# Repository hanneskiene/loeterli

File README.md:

## Parts needed
* Board
* JBC t245 handpiece
* Transformer 12-24V 50-120VA

## TODO
* Handle holder in pcb?
* Zero Cross Detection
* Termocouple Instrumentation Amp Layout
* Overcurrent Detection with shunt
* Connector for external sleep input + sleep in middle stand
* FUSE to earth

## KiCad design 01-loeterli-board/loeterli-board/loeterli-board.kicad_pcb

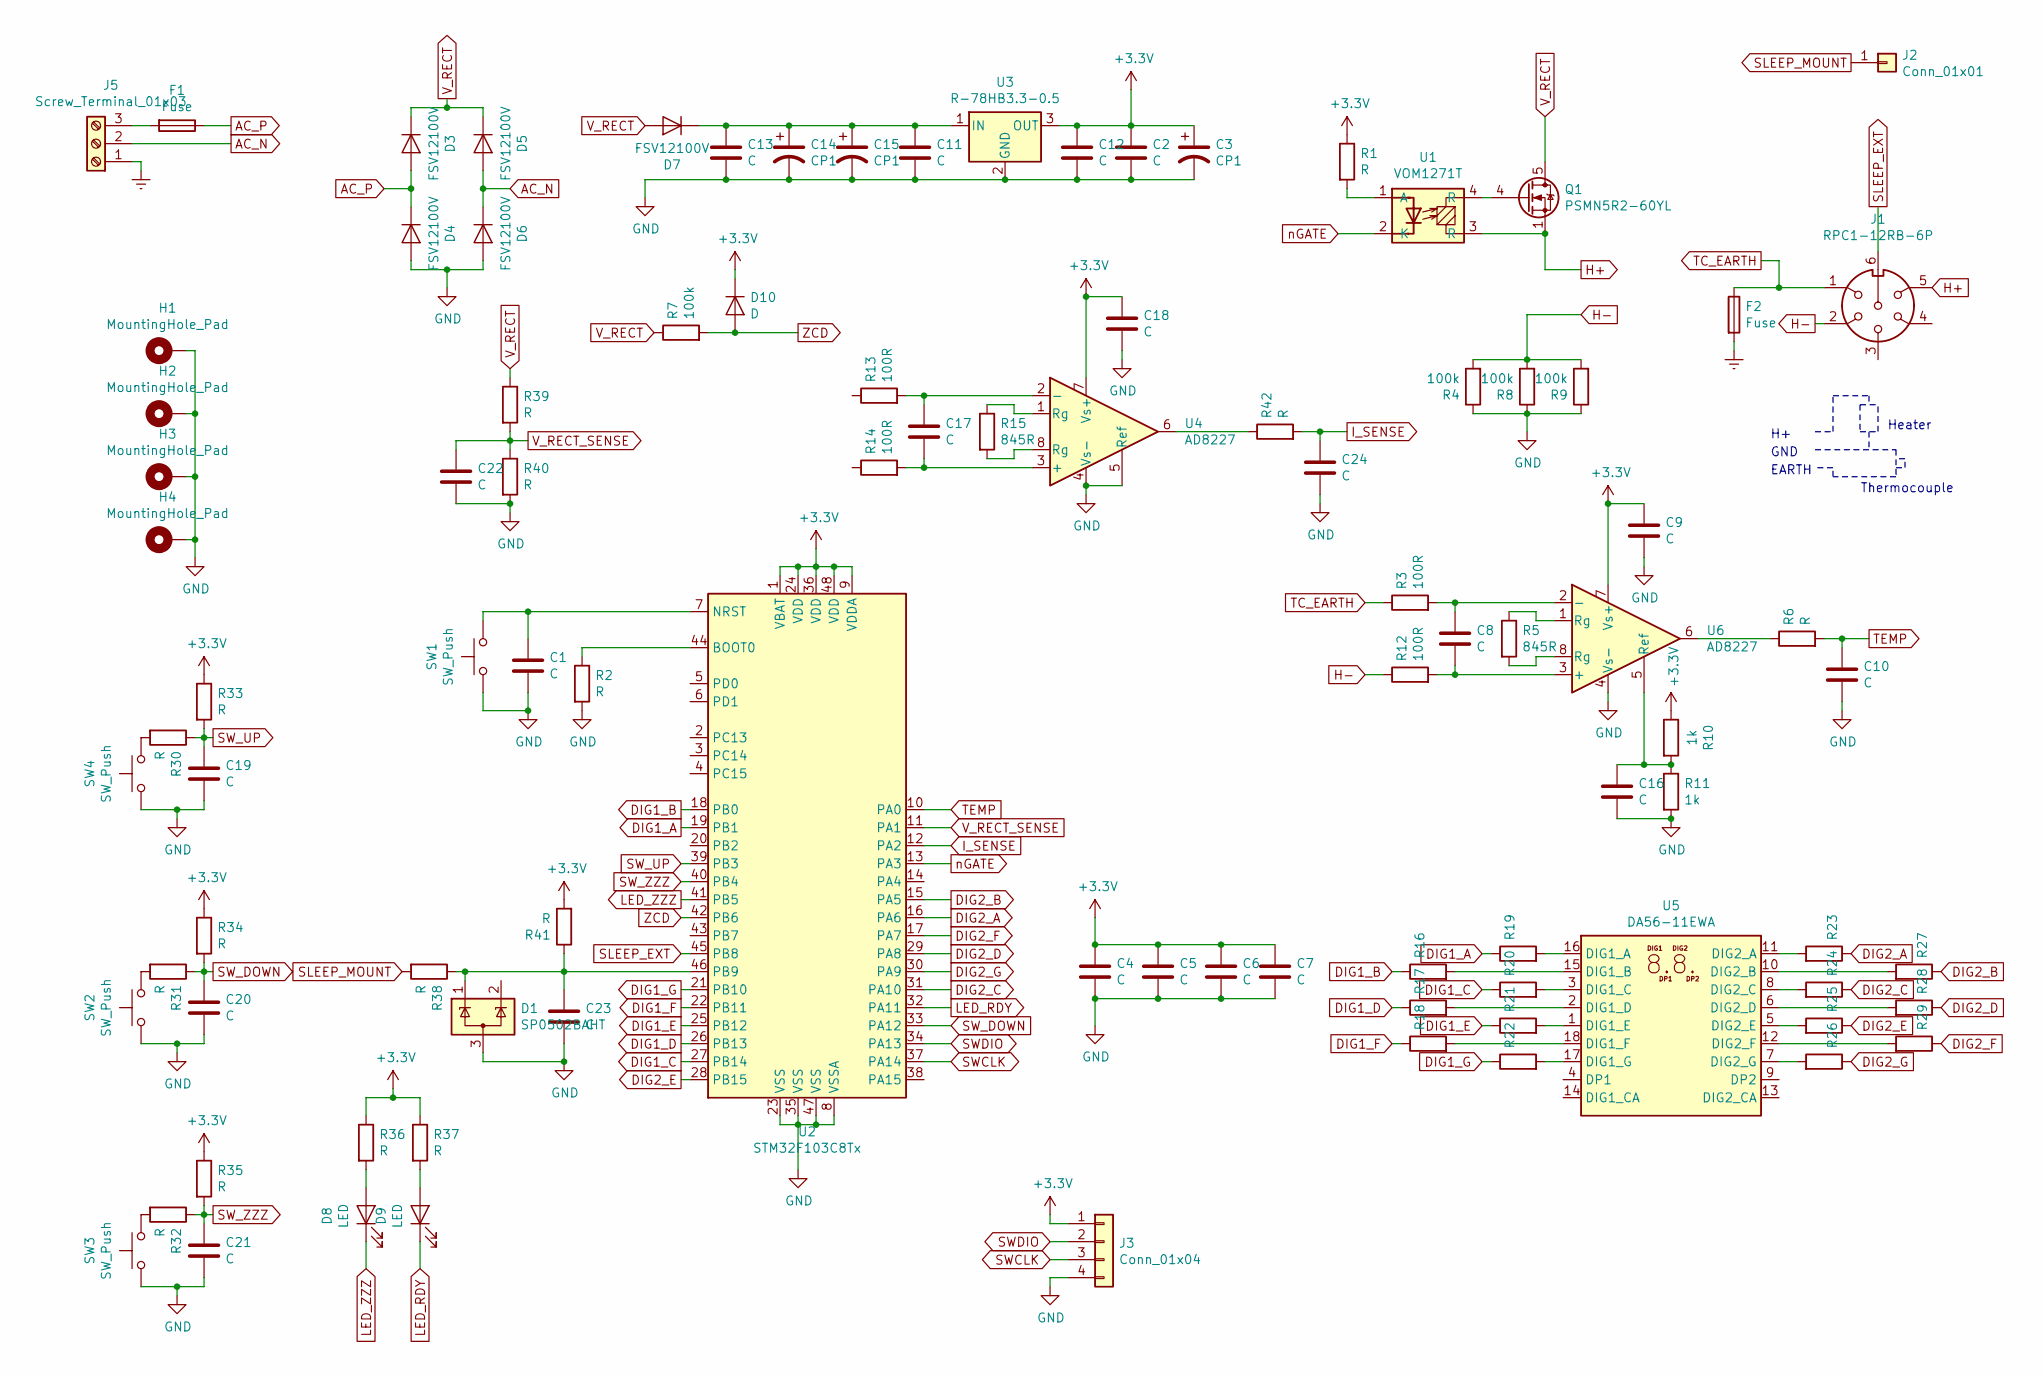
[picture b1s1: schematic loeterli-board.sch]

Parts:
C1, C2, C11, C12, C13: C; C_1206_3216Metric
C3, C14, C15: CP1; CP_Radial_D10.0mm_P5.00mm_P7.50mm
C4, C5, C6, C7, C8, C9, C10, C16, C17, C18, C19, C20, C21, C22, C23, C24: C; C_0603_1608Metric
D1: SP0502BAHT; SOT-23
D3, D4, D5, D6, D7: FSV12100V; TO-277A
D8, D9: LED; LED_D4.0mm
D10: D; D_0603_1608Metric
F1: Fuse; Fuseholder_Cylinder-5x20mm_Schurter_0031_8201_Horizontal_Op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
F2: Fuse; Fuse_1206_3216Metric
H1, H2, H3, H4: MountingHole_Pad; MountingHole_3.2mm_M3_Pad_Via
J1: RPC1-12RB-6P
J2: Conn_01x01; handpiece-holder
J3: Conn_01x04; PinHeader_1x04_P2.54mm_Vertical
J5: Screw_Terminal_01x03; TerminalBlock_Phoenix_MKDS-1,5-3-5.08_1x03_P5.08mm_Horizont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
Q1: PSMN5R2-60YL; LFPAK56
R1: R; R_1206_3216Metric
R2, R6, R30, R31, R32, R33, R34, R35, R36, R37, R38, R39, R40, R41, R42: R; R_0603_1608Metric
R3, R12, R13, R14: 100R; R_0603_1608Metric
R4, R7, R8, R9: 100k; R_1206_3216Metric
R5, R15: 845R; R_0603_1608Metric
R10, R11: 1k; R_0603_1608Metric
R16, R17, R18, R19, R20, R21, R22, R23, R24, R25, R26, R27, R28, R29: 680R; R_0603_1608Metric
SW1: SW_Push; SW_PUSH_6mm_H4.3mm
SW2, SW3, SW4: SW_Push; SW_PUSH_6mm_H7.3mm
U1: VOM1271T; SOP-4_3.8x4.1mm_P2.54mm
U2: STM32F103C8Tx; LQFP-48_7x7mm_P0.5mm
U3: R-78HB3.3-0.5; Converter_DCDC_RECOM_R-78HB-0.5_THT
U4, U6: AD8227; MSOP-8_3x3mm_P0.65mm
U5: DA56-11EWA; DA56-11SURKWA

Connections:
+3V3: C2.1, C3.1, C4.1, C5.1, C6.1, C7.1, C9.1, C12.1, C18.1, D10.1 (K), J3.1, R1.1, R10.1, R33.1, R34.1, R35.1, R36.1, R37.1, R41.2, U2.1 (VBAT), U2.9 (VDDA), U2.24 (VDD), U2.36 (VDD), U2.48 (VDD), U3.3 (OUT), U4.7 (Vs+), U6.7 (Vs+)
AC_N: D5.1 (A), D5.2 (A), D6.3 (K), J5.2
AC_P: D3.1 (A), D3.2 (A), D4.3 (K), F1.1
DIG1_A: R19.1, U2.19 (PB1)
DIG1_B: R16.1, U2.18 (PB0)
DIG1_C: R20.1, U2.27 (PB14)
DIG1_D: R17.1, U2.26 (PB13)
DIG1_E: R21.1, U2.25 (PB12)
DIG1_F: R18.1, U2.22 (PB11)
DIG1_G: R22.1, U2.21 (PB10)
DIG2_A: R23.1, U2.16 (PA6)
DIG2_B: R27.1, U2.15 (PA5)
DIG2_C: R24.1, U2.31 (PA10)
DIG2_D: R28.1, U2.29 (PA8)
DIG2_E: R25.1, U2.28 (PB15)
DIG2_F: R29.1, U2.17 (PA7)
DIG2_G: R26.1, U2.30 (PA9)
Earth: F2.2, J5.1
GND: C1.2, C2.2, C3.2, C4.2, C5.2, C6.2, C7.2, C9.2, C10.2, C11.2, C12.2, C13.2, C14.2, C15.2, C16.2, C18.2, C19.2, C20.2, C21.2, C22.2, C23.2, C24.2, D1.3 (A), D4.1 (A), D4.2 (A), D6.1 (A), D6.2 (A), H1.1, H2.1, H3.1, H4.1, J3.4, R2.2, R4.1, R8.1, R9.1, R11.2, R40.2, SW1.1, SW2.1, SW3.1, SW4.1, U2.8 (VSSA), U2.23 (VSS), U2.35 (VSS), U2.47 (VSS), U3.2 (GND), U4.4 (Vs-), U4.5 (Ref), U6.4 (Vs-)
H+: J1.5, Q1.1 (S), Q1.2 (S), Q1.3 (S), U1.3 (R)
H-: J1.2, R4.2, R8.2, R9.2, R12.1
I_SENSE: C24.1, R42.2, U2.12 (PA2)
LED_RDY: D9.1 (K), U2.32 (PA11)
LED_ZZZ: D8.1 (K), U2.41 (PB5)
unnamed: C1.1, SW1.2, U2.7 (NRST)
unnamed: C8.1, R3.2, U6.2 (-)
unnamed: C8.2, R12.2, U6.3 (+)
unnamed: C11.1, C13.1, C14.1, C15.1, D7.3 (K), U3.1 (IN)
unnamed: C16.1, R10.2, R11.1, U6.5 (Ref)
unnamed: C17.1, R13.2, U4.2 (-)
unnamed: C17.2, R14.2, U4.3 (+)
unnamed: C23.1, D1.1 (K), R38.1, R41.1, U2.46 (PB9)
unnamed: D8.2 (A), R36.2
unnamed: D9.2 (A), R37.2
unnamed: F1.2, J5.3
unnamed: Q1.4 (G), U1.4 (R)
unnamed: R1.2, U1.1 (A)
unnamed: R2.1, U2.44 (BOOT0)
unnamed: R5.1, U6.1 (Rg)
unnamed: R5.2, U6.8 (Rg)
unnamed: R6.1, U6.6
unnamed: R15.1, U4.1 (Rg)
unnamed: R15.2, U4.8 (Rg)
unnamed: R16.2, U5.15 (DIG1_B)
unnamed: R17.2, U5.2 (DIG1_D)
unnamed: R18.2, U5.18 (DIG1_F)
unnamed: R19.2, U5.16 (DIG1_A)
unnamed: R20.2, U5.3 (DIG1_C)
unnamed: R21.2, U5.1 (DIG1_E)
unnamed: R22.2, U5.17 (DIG1_G)
unnamed: R23.2, U5.11 (DIG2_A)
unnamed: R24.2, U5.8 (DIG2_C)
unnamed: R25.2, U5.5 (DIG2_E)
unnamed: R26.2, U5.7 (DIG2_G)
unnamed: R27.2, U5.10 (DIG2_B)
unnamed: R28.2, U5.6 (DIG2_D)
unnamed: R29.2, U5.12 (DIG2_F)
unnamed: R30.2, SW4.2
unnamed: R31.2, SW2.2
unnamed: R32.2, SW3.2
unnamed: R42.1, U4.6
SLEEP_EXT: J1.6, U2.45 (PB8)
SLEEP_MOUNT: J2.1, R38.2
SWCLK: J3.3, U2.37 (PA14)
SWDIO: J3.2, U2.34 (PA13)
SW_DOWN: C20.1, R31.1, R34.2, U2.33 (PA12)
SW_UP: C19.1, R30.1, R33.2, U2.39 (PB3)
SW_ZZZ: C21.1, R32.1, R35.2, U2.40 (PB4)
TC_EARTH: F2.1, J1.1, R3.1
TEMP: C10.1, R6.2, U2.10 (PA0)
V_RECT: D3.3 (K), D5.3 (K), D7.1 (A), D7.2 (A), Q1.5 (D), R7.1, R39.1
V_RECT_SENSE: C22.1, R39.2, R40.1, U2.11 (PA1)
ZCD: D10.2 (A), R7.2, U2.42 (PB6)
nGATE: U1.2 (K), U2.13 (PA3)

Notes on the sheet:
Thermocouple
Heater
EARTH
GND

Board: 2 copper layers, 96 parts (0 on the bottom side), 74 nets, no tracks yet.

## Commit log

2020-05-22 initial
2020-05-23 new ac rect arch
2020-05-23 sym table
2020-05-23 loetstecker footprint
2020-05-23 added readme image + misc
2020-05-23 updated image
2020-05-23 more
2020-05-23 todo
2020-05-23 readme
2020-05-24 misc
2020-05-24 image
2020-05-25 thermocouple circuit instr and sim
2020-05-25 readme chg
2020-05-25 folder for sim
2020-05-25 changed tc amp
2020-05-28 logo + res for leds
2020-05-28 updated logo
2020-05-29 SWD connector
2020-05-30 pinbelegung etc
2020-06-07 layout
2020-06-08 layout changes
